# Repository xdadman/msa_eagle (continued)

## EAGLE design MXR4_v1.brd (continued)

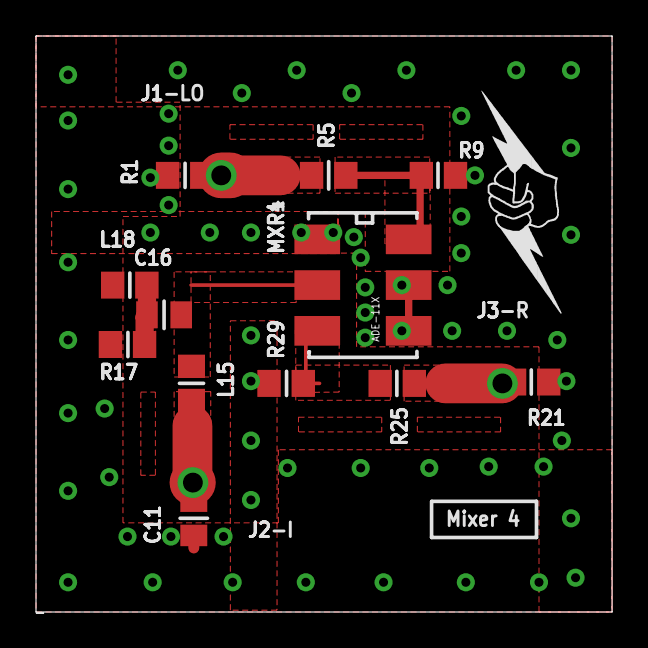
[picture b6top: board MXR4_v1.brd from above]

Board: 2 copper layers, 32.0 x 32.0 mm, 15 parts (0 on the bottom side), 8 nets.

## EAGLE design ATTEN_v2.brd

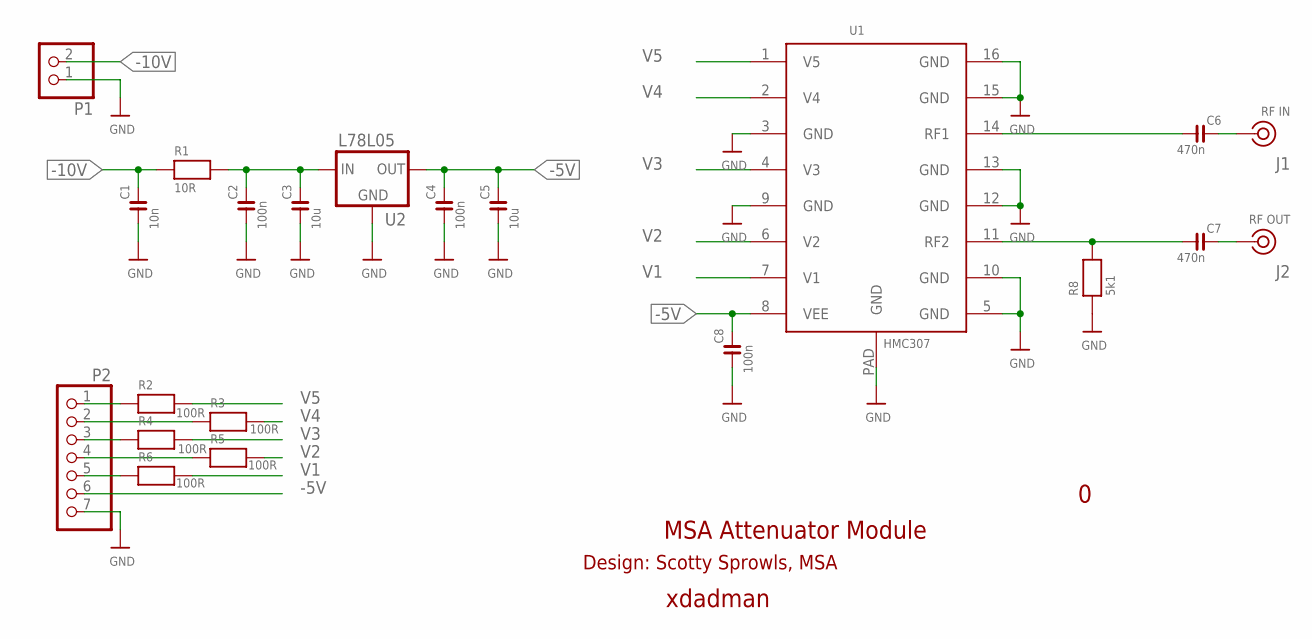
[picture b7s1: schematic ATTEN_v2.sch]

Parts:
C1: 10n; C0805
C2, C4, C8: 100n; C0805
C3, C5: 10u; 1206
C6, C7: 470n; C0805
J1: RF IN; SLIM_COAX_PAD
J2: RF OUT; SLIM_COAX_PAD
P1: PINHD-1X2; 1X02
P2: PINHD-1X7; 1X07
R1: 10R; R0805
R2, R3, R4, R5, R6: 100R; R0402
R8: 5k1; R0402
U1: HMC307; QSOP16_PAD
U2: L78L05; SOT89

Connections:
-5V: C4.2, C5.2, C8.2, P2.6, U1.8 (VEE), U2.3 (OUT)
-10V: C1.2, P1.2, R1.1
GND: C1.1, C2.1, C3.1, C4.1, C5.1, C8.1, J1.GND, J2.GND, P1.1, P2.7, R8.1, U1.3 (GND), U1.5 (GND), U1.9 (GND), U1.10 (GND), U1.12 (GND), U1.13 (GND), U1.15 (GND), U1.16 (GND), U1.PAD (GND), U2.1 (GND)
INV1: P2.5, R6.1
INV2: P2.4, R5.1
INV3: P2.3, R4.1
INV4: P2.2, R3.1
INV5: P2.1, R2.1
unnamed: C2.2, C3.2, R1.2, U2.2 (IN), U2.4 (IN)
unnamed: C6.2, J1.SIG (1)
unnamed: C7.2, J2.SIG (1)
unnamed: C7.1, R8.2, U1.11 (RF2)
unnamed: C6.1, U1.14 (RF1)
V1: R6.2, U1.7 (V1)
V2: R5.2, U1.6 (V2)
V3: R4.2, U1.4 (V3)
V4: R3.2, U1.2 (V4)
V5: R2.2, U1.1 (V5)

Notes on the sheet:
xdadman
MSA Attenuator Module
Design: Scotty Sprowls, MSA

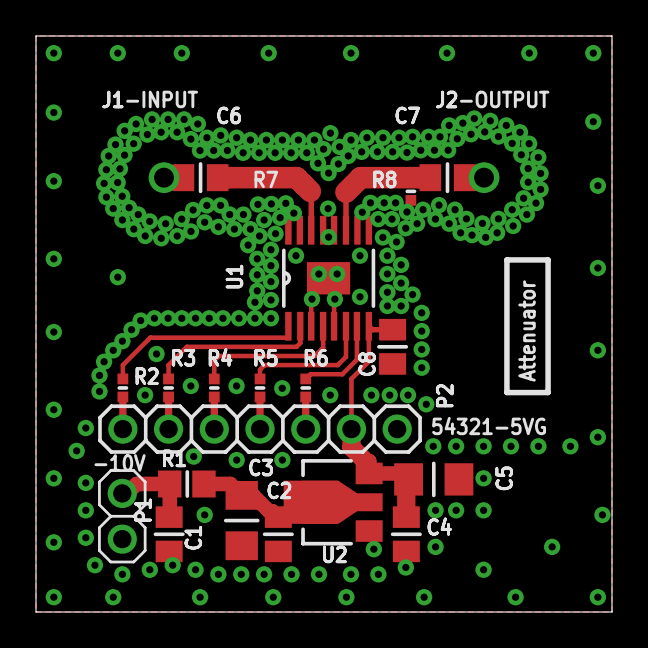
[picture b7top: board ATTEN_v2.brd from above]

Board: 2 copper layers, 32.0 x 32.0 mm, 21 parts (0 on the bottom side), 18 nets.

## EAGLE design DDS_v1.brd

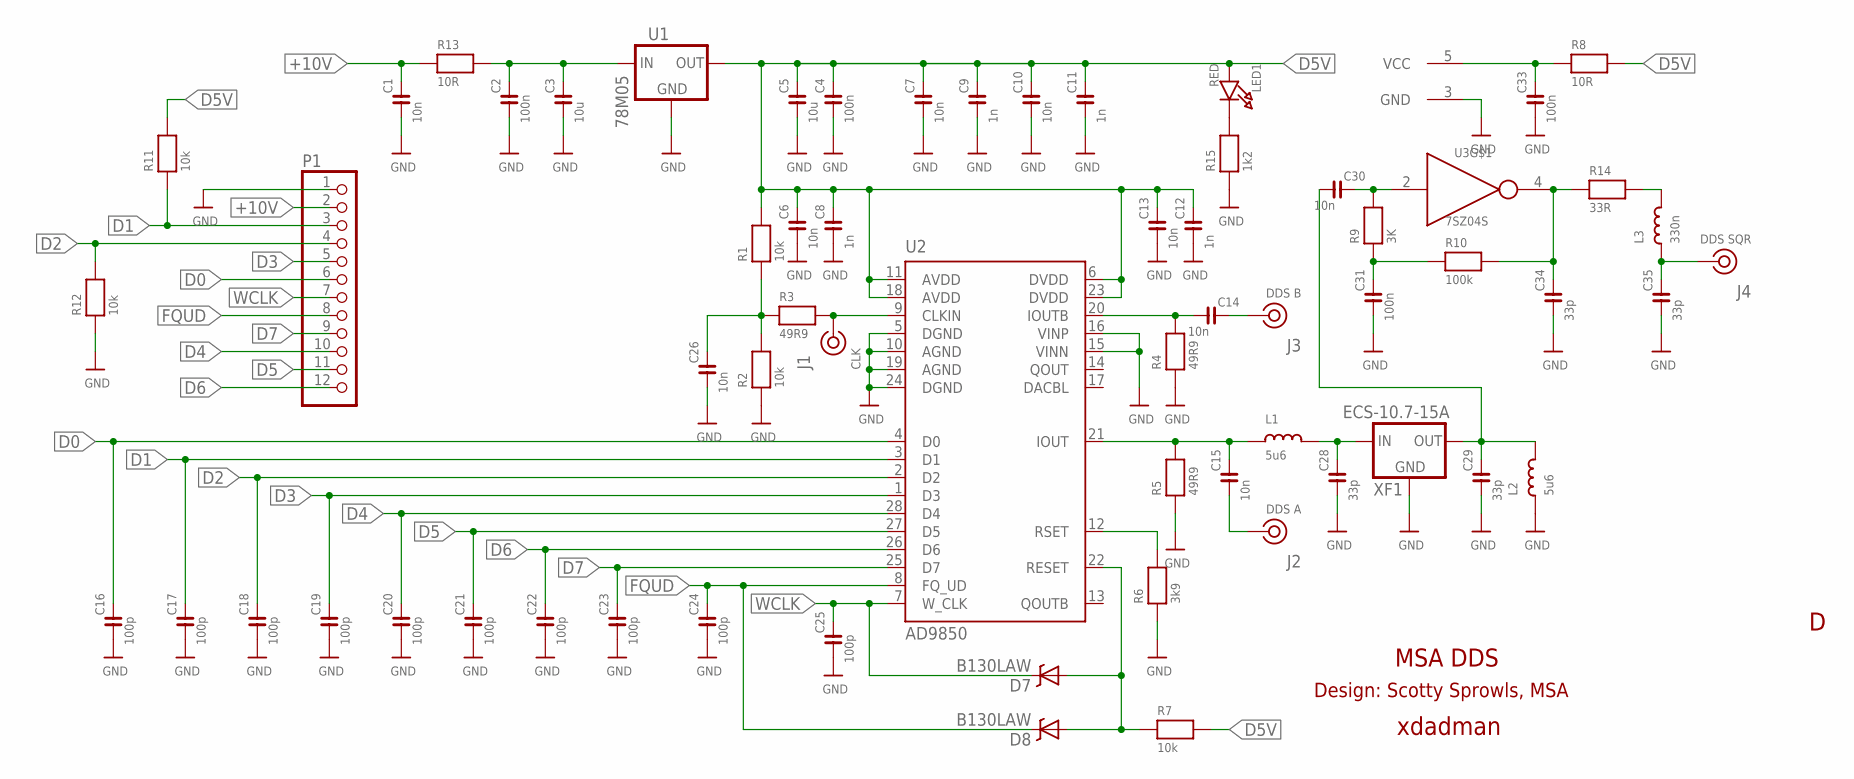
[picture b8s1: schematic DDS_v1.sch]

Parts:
C1, C6, C7, C10, C13, C14, C15, C26, C30: 10n; C0805
C2, C4, C31, C33: 100n; C0805
C3, C5: 10u; C1206
C8, C9, C11, C12: 1n; C0805
C16, C17, C18, C19, C20, C21, C22, C23, C24, C25: 100p; C0805
C28, C29, C34, C35: 33p; C0805
D7, D8: B130LAW; SOD-123
J1: CLK; SLIM_COAX_PAD
J2: DDS A; SLIM_COAX_PAD
J3: DDS B; SLIM_COAX_PAD
J4: DDS SQR; SLIM_COAX_PAD
L1, L2: 5u6; L805
L3: 330n; L805
LED1: RED; CHIPLED_0603
P1: PINHD-1X12; 1X12
R1, R2, R7, R11, R12: 10k; R0805
R3, R4, R5: 49R9; R0805
R6: 3k9; R0805
R8, R13: 10R; R0805
R9: 3K; R0805
R10: 100k; R0805
R14: 33R; R0805
R15: 1k2; R0805
U1: 78M05; TO252
U2: AD9850; SSOP28
U3: 7SZ04S; SOT23-5L
XF1: ECS-10.7-15A; XTALFILTER

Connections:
+10V: C1.2, P1.2, R13.1
D0: C16.2, P1.6, U2.4 (D0)
D1: C17.2, P1.3, R11.1, U2.3 (D1)
D2: C18.2, P1.4, R12.2, U2.2 (D2)
D3: C19.2, P1.5, U2.1 (D3)
D4: C20.2, P1.10, U2.28 (D4)
D5: C21.2, P1.11, U2.27 (D5)
D5V: C4.2, C5.2, C6.2, C7.2, C8.2, C9.2, C10.2, C11.2, C12.2, C13.2, LED1.A, R1.2, R7.2, R8.2, R11.2, U1.2 (OUT), U2.6 (DVDD), U2.11 (AVDD), U2.18 (AVDD), U2.23 (DVDD)
D6: C22.2, P1.12, U2.26 (D6)
D7: C23.2, P1.9, U2.25 (D7)
FQUD: C24.2, D8.C, P1.8, U2.8 (FQ_UD)
GND: C1.1, C2.1, C3.1, C4.1, C5.1, C6.1, C7.1, C8.1, C9.1, C10.1, C11.1, C12.1, C13.1, C16.1, C17.1, C18.1, C19.1, C20.1, C21.1, C22.1, C23.1, C24.1, C25.1, C26.1, C28.1, C29.1, C31.1, C33.1, C34.1, C35.1, J1.GND, J2.GND, J3.GND, J4.GND, L2.1, P1.1, R2.1, R4.1, R5.1, R6.1, R12.1, R15.1, U1.3 (GND), U2.5 (DGND), U2.10 (AGND), U2.15 (VINN), U2.16 (VINP), U2.19 (AGND), U2.24 (DGND), U3.3 (GND), XF1.3 (GND)
unnamed: C30.2, R9.2, U3.2 (IN)
unnamed: C33.2, R8.1, U3.5 (VCC)
unnamed: C15.2, L1.1, R5.2, U2.21 (IOUT)
unnamed: C26.2, R1.1, R2.2, R3.1
unnamed: C35.2, J4.SIG (1), L3.1
unnamed: C14.2, J3.SIG (1)
unnamed: C14.1, R4.2, U2.20 (IOUTB)
unnamed: D7.A, D8.A, R7.1, U2.22 (RESET)
unnamed: C2.2, C3.2, R13.2, U1.1 (IN)
unnamed: R6.2, U2.12 (RSET)
unnamed: C15.1, J2.SIG (1)
unnamed: C28.2, L1.2, XF1.2 (IN)
unnamed: C31.2, R9.1, R10.1
unnamed: C29.2, C30.1, L2.2, XF1.1 (OUT)
unnamed: L3.2, R14.2
unnamed: C34.2, R10.2, R14.1, U3.4 (OUT)
unnamed: LED1.C, R15.2
unnamed: J1.SIG (1), R3.2, U2.9 (CLKIN)
WCLK: C25.2, D7.C, P1.7, U2.7 (W_CLK)

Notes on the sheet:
xdadman
MSA DDS
Design: Scotty Sprowls, MSA

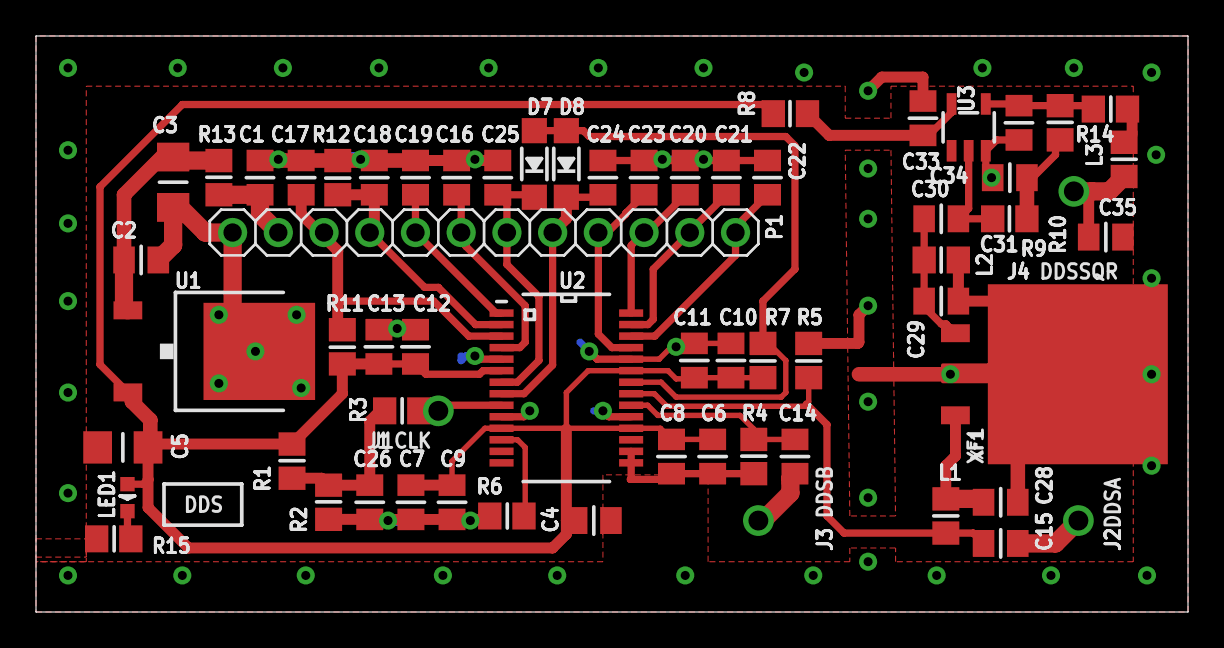
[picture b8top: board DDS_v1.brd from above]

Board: 2 copper layers, 64.0 x 32.0 mm, 63 parts (0 on the bottom side), 31 nets.

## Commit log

2015-04-06 Initial
2015-04-09 Readme update
